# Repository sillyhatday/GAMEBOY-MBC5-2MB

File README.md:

# GAMEBOY-FLASHCART-MBC5 2MB

A working PCB layout for making your own MBC5 2MB based Gameboy cartridge. Final version fully tested. Unless there is an issue that comes up, then consider this complete.

>[!NOTE]
>If you are looking for a first cartridge to build yourself, then this is it.

>[!TIP]
>Compatible with GBxCart and FlashGBX

## ⚪ Game Compatibility

[COMPATIBILTY LIST](MBC5-FLASH-COMMPAT.txt)

Nearly all Gameboy colour games used this memory mapper. It can address up to 8MB of game storage and up to 128KB of game save storage. This one only using 2MB of ROM and 32KB of RAM. 95% of GBC games using this mapper are within this range. Most 8KB save files should work fine on the 32KB chip also. 

Earlier games from the DMG should work, Nintendo kept each revision of mapper compatible with the previous (for the most part). So long as programmers followed Nintendos suggestions when developing. Mole Mania wasn't designed for an MBC5 and works perfectly, yet Zelda - Links Awakening doesn't, it crashes when saving.

>[!WARNING]
>This cart will not work properly for real time clock games. This means games like Pokemon G/S/C.

## 📷 Photos

## 🟣 Bill of materials:

>[!IMPORTANT]
>When ordering PCBs, be sure to order in 0.8mm thickness with gold plating!

| Part | Quantity |
|--------------|----|
| 29F016 Flash | x1 |
| FM1808 or FM18W08* | x1 |
| MBC5 | x1 |
| SN74LVC1G332DBVR | x1 (OPTIONAL) |
| 10K 0603 resistor | x2 |
| 0.1uF 0603 capacitor | x4 |

**FM18L08 will work but is not suggested*

### 💻 EEPROM 29F016B <br>
I've found them available from Aliexpress very easily. Lately the prices of these have risen. Once available for about £1 per chip are not £1.60 per chip. These are a 16-bit address and 8-bit data bus EEPROM. The write enable pin is brought to the audio pin on the Gameboy cartridge header. This is compatible with the GBxCart RW. The pin is held to 5v to keep it disabled during usage through a pullup resistor.

### 🐏 FRAM FM1808 <br>
These are expensive. Current prices are €11.90 from Mouser. They are available for much less on Aliexpress, for the same price you can get 5 - 10. These are known to be ***extremely*** unreliable. You are likely buying factory rejects that don't fully work or meet the speed rating. In a batch of 5 from Aliexpress I got, none of them worked. Another 10 I got, I went through 4 before finding a working one. In the end I went through 8 chips before getting one that works. The cost of 9 dodgy chips was more than one from Mouser.

### ❗OR Gate SN74LVC1G332DBVR
I consider this optional but reccomended. In my testing, I have not found that games under 2MB in size require extra glue logic. I'd still use it to be confident that your game saves will be safe.

### ❔ Memory Controller MBC5 <br>
You used to be able to go on eBay and find trash games for €3 easily, some deals I've had as low as €1. I could go on eBay and grab one or two of them per week. They seem to have gone up and the best deals are about €5 now. You'll need a hot air station to remove the chip from the board.

## CHANGE LOG <br>
| Date | Notes |
| ---- | ----- |
| 30/11/23 | Last update was not final. This should hopefully be final. More tastful logo design on the cart now. I've spend ages making sure the holes in the PCB are the same as factory Nintendo PCB. They should actually fit in Nintendo shells now with the small top locating pin. Nothing more to add now. I've actually got some of these on order for myself. Last ones I had made were V1.2 |
| 08/05/23 | Big update. Added OR gate for better MBC1 compatibility, which can be bypassed if not desired. Moved nearly every trace to reduce vias and improve appearance. Likely final update unless there is a problem. |
| 08/04/23 | Changed fill edge limits to right values for new KiCad version. Changed Sillyhatday rear label to be more subtle. |
| 10/03/23 | Updated the top edge cut drill hole. Doesn't quite fit in shells with the top stud properly. It should now, but is untested. |
| 05/03/23 | Update to V1.4. Changed some tiny errors in trace routing, invisible but bugged me. Changed MBC and ROM footprints to standard library footprints. |
| 07/02/23 | Updated to V1.3. Adjusted some trace routes for a better looking board. Added missing capacitor value to board for C4. Added many games to compatibility list. |
| 21/01/23 | Updated to V1.2. The Board size has been adjusted to better fit into cartridge shells. Also added extra 5v trace. |
| 15/01/23 | Updated Readme in the FRAM section and the end section. Cypress is a the newer name for Ramtron, it's definitly a problem with junk parts not Cypress chips. Also added more to the compatability list. |
| 31/05/22 | Not a change as such. I've had problems with Cypress branded FRAM. I Haven't determined if it is bad quality or fake chips. Right now, I suggest sticking with Ramtron branded FRAM. All kinds of strange behavior is to be expected. |
| 24/04/22 | Noticed a mistake in 5v top plane. Not sure how this hasn't caused problems. Also changed routing of some grounds and 5v traces. |
| 20/03/22 | First Revision uploaded. A few hours of testing done, everything worked as expected. Built 10 of these original versions. |

## Links

🏷️ NextStopPlease Labels: https://nextstopplease.square.site/ <br>
📷 NextStopPlease Insta: https://www.instagram.com/nxt.stop.please/ <br>
🛍️ Inside Gadgets Shop: https://shop.insidegadgets.com <br>
📎 Inside Gadgets GitHub: https://github.com/insidegadgets <br>
📷 Inside Gadgets Insta: https://www.instagram.com/inside.gadgets <br>
🖇️ Bytendo Mods GitHub: https://github.com/bytendomods <br>
🐭 Bucket Mouse: https://github.com/Bucket-Mouse <br>
🛒 Natalie Shop: https://nataliethenerd.com/ <br>
🤓 Natalie GitHub: https://github.com/natalie-lang/natalie <br>

## ⚖️ License

This work is licensed under a Creative Commons Attribution-ShareAlike 4.0 International License. You are able to copy and redistribute the material in any medium or format, as well as remix, transform, or build upon the material for any purpose (even commercial) - but you must give appropriate credit, provide a link to the license, and indicate if any changes were made.

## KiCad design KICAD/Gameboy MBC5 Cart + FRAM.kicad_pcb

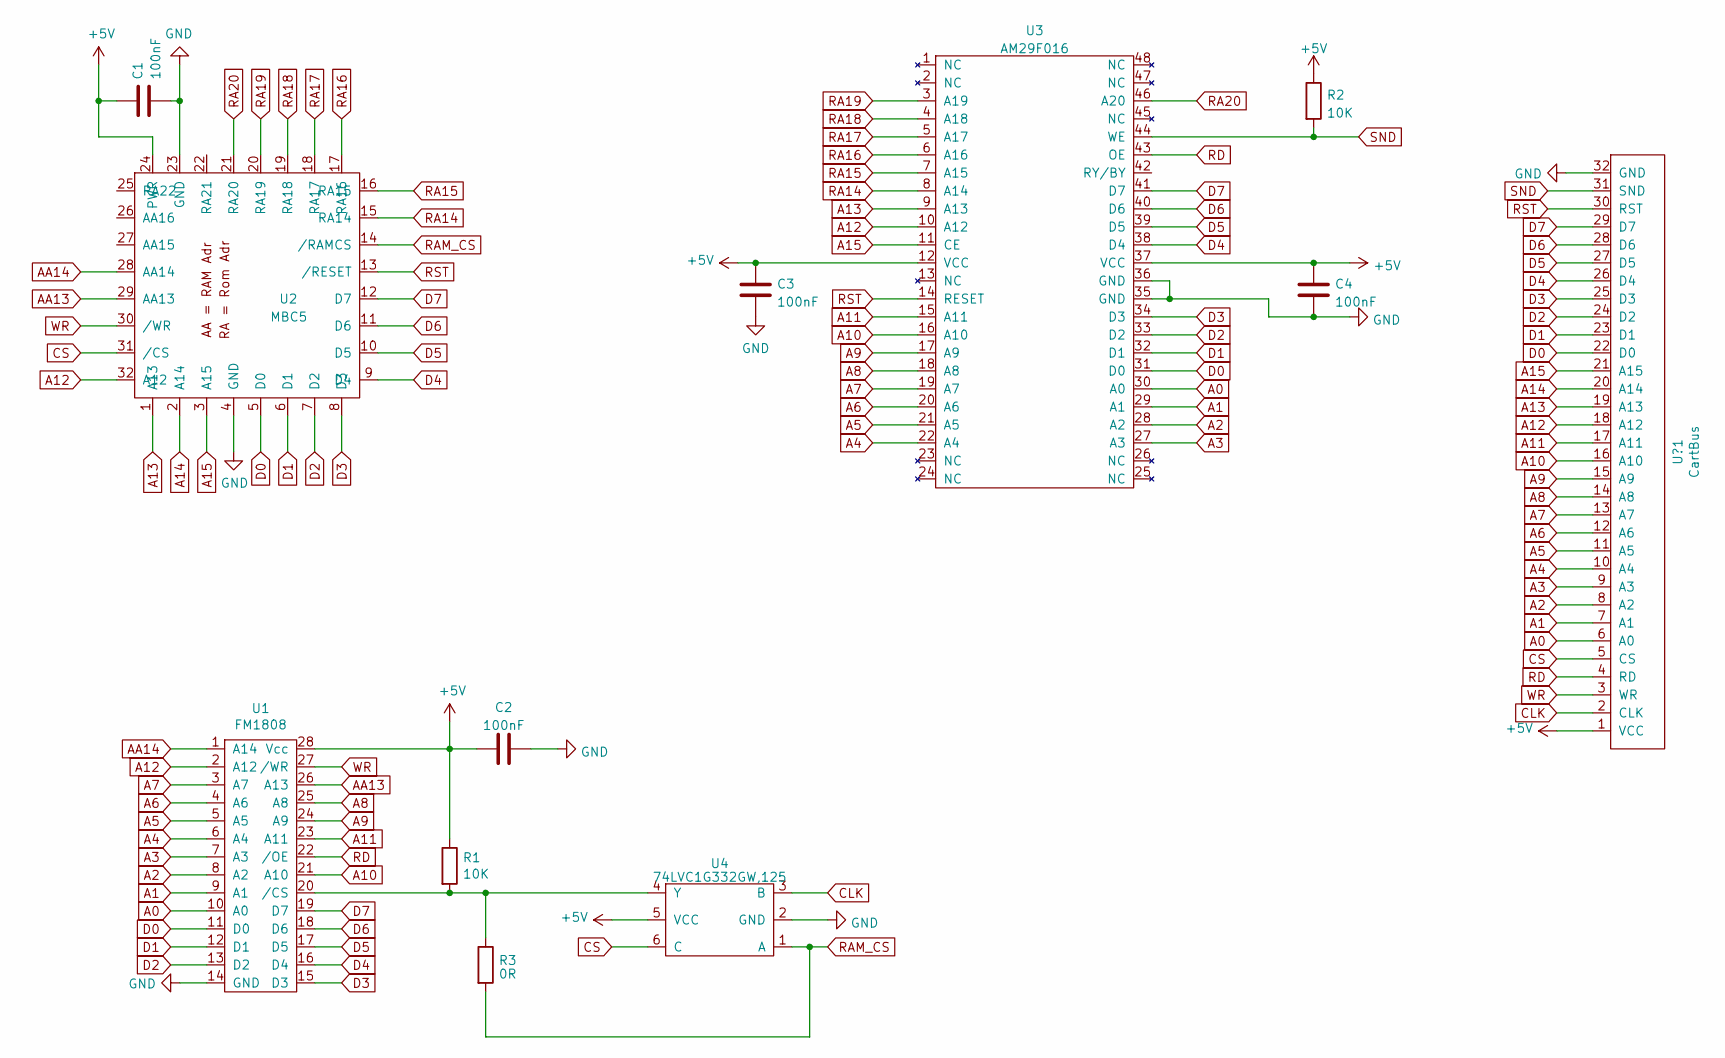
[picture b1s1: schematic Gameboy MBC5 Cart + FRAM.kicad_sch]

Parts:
C1, C2, C3, C4: 100nF; C_0603_1608Metric_Pad1.08x0.95mm_HandSolder
R1, R2: 10K; R_0603_1608Metric_Pad0.98x0.95mm_HandSolder
R3: 0R; LINK
U1: FM1808; SOIC-28W_7.5x17.9mm_P1.27mm
U2: MBC5; LQFP-32_7x7mm_P0.8mm
U3: AM29F016; TSOP-I-48_18.4x12mm_P0.5mm
U4: 74LVC1G332GW,125; TSOP-6_1.65x3.05mm_P0.95mm
U?1: CartBus; GameBoy_GamePak_DMG-09_P1.50mm_Edge

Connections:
+5V: C1.1, C2.1, C3.1, C4.1, R1.1, R2.1, U1.28 (Vcc), U2.24 (PWR), U3.12 (VCC), U3.37 (VCC~), U4.5 (VCC), U?1.1 (VCC)
A0: U1.10 (A0), U3.30 (A0~), U?1.6 (A0)
A1: U1.9 (A1), U3.29 (A1), U?1.7 (A1)
A2: U1.8 (A2), U3.28 (A2), U?1.8 (A2)
A3: U1.7 (A3), U3.27 (A3), U?1.9 (A3)
A4: U1.6 (A4), U3.22 (A4), U?1.10 (A4)
A5: U1.5 (A5), U3.21 (A5), U?1.11 (A5)
A6: U1.4 (A6), U3.20 (A6), U?1.12 (A6)
A7: U1.3 (A7), U3.19 (A7), U?1.13 (A7)
A8: U1.25 (A8), U3.18 (A8), U?1.14 (A8)
A9: U1.24 (A9), U3.17 (A9), U?1.15 (A9)
A10: U1.21 (A10), U3.16 (A10), U?1.16 (A10)
A11: U1.23 (A11), U3.15 (A11), U?1.17 (A11)
A12: U1.2 (A12), U2.32 (A12), U3.10 (A12), U?1.18 (A12)
A13: U2.1 (A13), U3.9 (A13), U?1.19 (A13)
A14: U2.2 (A14), U?1.20 (A14)
A15: U2.3 (A15), U3.11 (CE), U?1.21 (A15)
AA13: U1.26 (A13), U2.29 (AA13)
AA14: U1.1 (A14), U2.28 (AA14)
CLK: U4.3 (B), U?1.2 (CLK~)
CS: U2.31 (/CS), U4.6 (C), U?1.5 (CS)
D0: U1.11 (D0), U2.5 (D0), U3.31 (D0), U?1.22 (D0)
D1: U1.12 (D1), U2.6 (D1), U3.32 (D1), U?1.23 (D1)
D2: U1.13 (D2), U2.7 (D2), U3.33 (D2), U?1.24 (D2)
D3: U1.15 (D3), U2.8 (D3), U3.34 (D3), U?1.25 (D3)
D4: U1.16 (D4), U2.9 (D4), U3.38 (D4), U?1.26 (D4)
D5: U1.17 (D5), U2.10 (D5), U3.39 (D5), U?1.27 (D5)
D6: U1.18 (D6), U2.11 (D6), U3.40 (D6), U?1.28 (D6)
D7: U1.19 (D7), U2.12 (D7), U3.41 (D7), U?1.29 (D7)
GND: C1.2, C2.2, C3.2, C4.2, U1.14 (GND), U2.4 (GND), U2.23 (GND), U3.35 (GND), U3.36 (GND), U4.2 (GND), U?1.32 (GND)
unnamed: R1.2, R3.1, U1.20 (/CS), U4.4 (Y)
RA14: U2.15 (RA14), U3.8 (A14)
RA15: U2.16 (RA15), U3.7 (A15)
RA16: U2.17 (RA16), U3.6 (A16)
RA17: U2.18 (RA17), U3.5 (A17)
RA18: U2.19 (RA18), U3.4 (A18)
RA19: U2.20 (RA19), U3.3 (A19)
RA20: U2.21 (RA20), U3.46 (A20)
RAM_CS: R3.2, U2.14 (/RAMCS), U4.1 (A)
RD: U1.22 (/OE), U3.43 (OE~), U?1.4 (RD)
RST: U2.13 (/RESET), U3.14 (RESET), U?1.30 (RST)
SND: R2.2, U3.44 (WE), U?1.31 (SND)
WR: U1.27 (/WR), U2.30 (/WR), U?1.3 (WR)

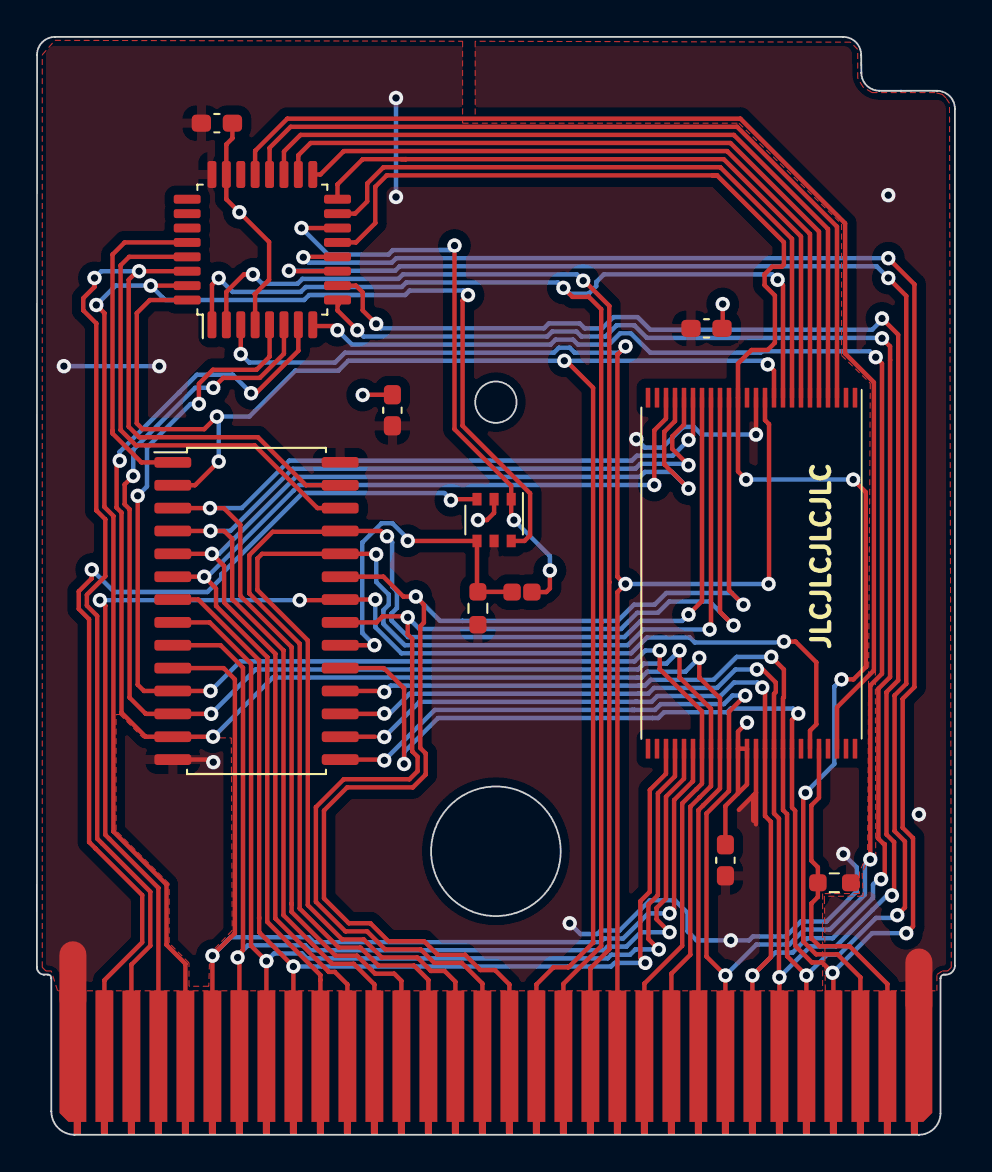
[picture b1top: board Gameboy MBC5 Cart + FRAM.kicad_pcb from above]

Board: 2 copper layers, 51.0 x 61.0 mm, 12 parts (0 on the bottom side), 43 nets.

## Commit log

2022-03-19 Update README.md
    First readme. Gerbers to follow
2023-11-30 Update README.md
    updated changelog
2023-12-14 Update README.md
    Final update bits and bobs
2023-12-14 Update README.md
    comment
2023-12-31 Update README.md
    new photos
2023-12-31 Update README.md
    New photos fixed
2023-12-31 Update README.md
    Fixed
2024-01-02 Update README.md
    Changed readme. Added game compatibility at the top and removed compatibility at the bottom
2025-05-28 Create License.md
    License added
2025-05-28 Update README.md
    added license
2026-06-24 Update README.md
    readme update for 2026
2026-06-24 Update README.md
    added links
2026-06-24 Update README.md
    typos, photo scaling
2026-06-24 Update README.md
    logic gate section
2026-06-24 Update README.md
    tip
2026-06-25 Create call this a design?
